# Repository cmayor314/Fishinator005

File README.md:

# Fishinator005
Fishinator005 is an **Aquaponic** system.  It is for growing both plants and fish together in a enclosed space
for the purposes of food.

## Aquaponics

Aquaponics is conservative of water; the only significant water loss is due to evaporation.
Two crops are fed for the price of one: you feed the fish and ammonia from their gills is plant food.

## What's here

The current working system is here, but still being filled in.
The documentation will take a long time.

The software/hardware includes a:

  - remote sense cluster
  
  - basic *local-to-Fishinator* control system running directly on Raspberry Pi + some hardware
  
  - basic RESTful interface on Raspberry Pi for control by Supervisor Flows
  
  - Supervisor system Control and Analysis on a remote machine with more computing power available
  
  - web-based UI

## Components:

### Supervisor 
- Control and analysis from remote machine with better computational ability via node-red and node.js

### FishinatorPi 
- currently Raspberry-pi implmentation of Fishinator direct control via node-red and node.js

### RemoteSense 
- Atmel Mega328p implementation of reading local sensors, sent directly to Fishinator
			-KiCAD schematic files (schematic complete, placement and routing not started)
			-arduino-interface code

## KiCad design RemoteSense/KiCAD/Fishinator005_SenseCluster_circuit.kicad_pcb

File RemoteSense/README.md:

This directory contains the **Remote Sense Cluster** for the fishinator.

This Sense Cluster is "remote" in the sense that it may be placed anywhere (within bluetooth range) with respect to the FishinatorPi (which controls the Fishinator), it is not connected by wire.  The Sense Cluster *must* be reasonably attached to the Fishinator, the system for which it senses.

The Fishinator uses this remote sense cluster to get data about light levels, temperatures, and a water-depth measurement.  Also available are voltage levels from the remote sense cluster circuit.

Via bluetooth serial, the remote sense cluster sends its data to the FishinatorPi device.

This directory includes:

  - the arduino-interface code (C/C++) for the ATMEL 328p microcontroller.
  - A subdirectory holds the (current state of) the KiCAD files for manufacturing a remote sense cluster printed circuit board.  

The KiCAD design is based on the prototype-board impementation with the Fishinator.

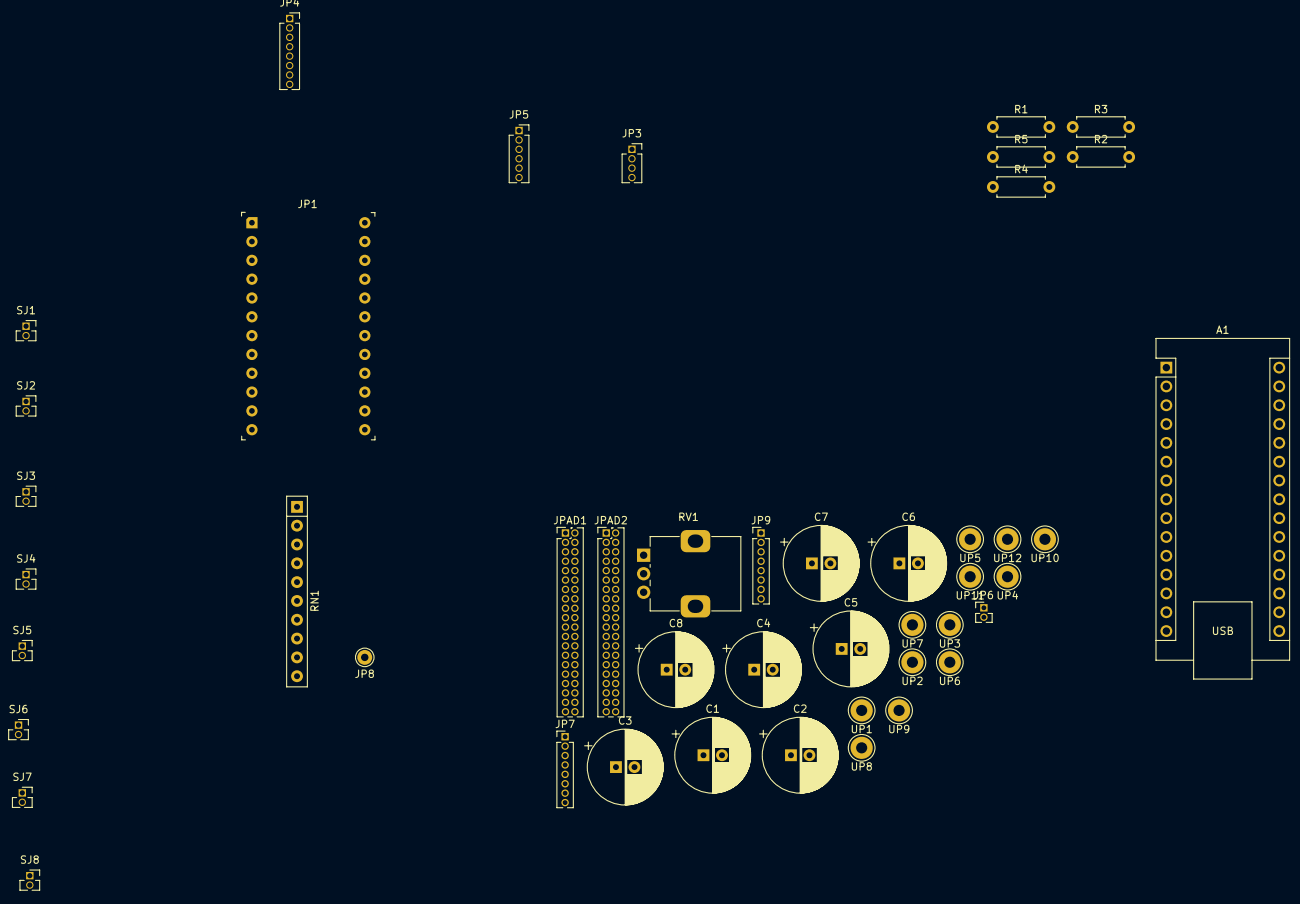
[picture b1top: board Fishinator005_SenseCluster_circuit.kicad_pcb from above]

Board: 2 copper layers, 46 parts (0 on the bottom side), 42 nets, no tracks yet.

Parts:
A1: Arduino_Nano_v3.x; Arduino_Nano
C1, C2, C3, C4, C5, C6, C7, C8: C_Polarized_US; CP_Radial_D10.0mm_P2.50mm
JP1: A_24-LC-TT; Socket_DIP-24_15.24mm_Conn
JP3: Conn_01x04_Male; PinSocket_1x04_P1.27mm_Vertical
JP4: Conn_01x08_Female; PinSocket_1x08_P1.27mm_Vertical
JP5: Conn_01x06_Female; PinSocket_1x06_P1.27mm_Vertical
JP6: Conn_01x02_Male; PinHeader_1x02_P1.27mm_Vertical
JP7, JP9: Conn_01x08; PinHeader_1x08_P1.27mm_Vertical
JP8: Conn_01x08; Pin_D1.0mm_L10.0mm
JPAD1, JPAD2: Conn_02x20_Counter_Clockwise; PinHeader_2x20_P1.27mm_Vertical
R1: 200R; R_Axial_DIN0207_L6.3mm_D2.5mm_P7.62mm_Horizontal
R2: 2k; R_Axial_DIN0207_L6.3mm_D2.5mm_P7.62mm_Horizontal
R3: 1k; R_Axial_DIN0207_L6.3mm_D2.5mm_P7.62mm_Horizontal
R4, R5: 0R; R_Axial_DIN0207_L6.3mm_D2.5mm_P7.62mm_Horizontal
RN1: R_Network09_US; R_Array_SIP10
RV1: 500R; Potentiometer_Alps_RK09K_Single_Vertical
SJ1, SJ2, SJ3, SJ4, SJ5, SJ6, SJ7, SJ8: Screw_Terminal_01x02; PinSocket_1x02_P1.27mm_Vertical
UP1, UP2, UP3, UP4, UP5, UP6, UP7, UP8, UP9, UP10, UP11, UP12: Conn_01x01; Pin_D1.3mm_L11.0mm_LooseFit

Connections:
+3V3: A1.17 (3V3), C1.1, C2.1, C3.1, JP1.21, JP4.7, JP7.6, RN1.1 (common)
+5V: A1.27 (+5V), C4.1, C5.1, C6.1, JP1.22, JP3.1, JP5.2
/CS: JP1.2, JP4.3, JP7.2
/DC: JP1.20, JP4.4, JP7.3, UP4.1
/EN: A1.9 (D6), JP1.19, R4.1, UP3.1
/MISO: JP1.4, JP7.8, UP5.1
/RST: JP1.1, JP4.2, JP7.1
/SCK: JP1.5, JP4.5, JP7.4
/SDA: JP1.3, JP4.6, JP7.5
/Sense1: A1.19 (A0), JP1.7, RN1.2 (R1), SJ1.2
/Sense2: A1.20 (A1), JP1.8, RN1.3 (R2), SJ2.2
/Sense3: A1.21 (A2), JP1.9, RN1.4 (R3), SJ3.2
/Sense4: A1.22 (A3), JP1.10, RN1.5 (R4), SJ4.2
/Sense5: A1.23 (A4), JP1.11, RN1.6 (R5), SJ5.2
/Sense6: A1.24 (A5), JP1.12, RN1.7 (R6), SJ6.2
/Sense7: A1.25 (A6), RN1.8 (R7), SJ7.2, UP9.1
/Sense8: A1.26 (A7), JP8.1, RN1.9 (R8), SJ8.2, UP10.1
/Vref: A1.18 (AREF), JP1.6, UP6.1
/arRx: A1.2 (D0/RX), JP1.14, JP5.4
/arTx: A1.1 (D1/TX), JP1.15, JP5.5
/echo: A1.7 (D4), JP1.17, JP6.2, R2.1, R3.1
/state: A1.6 (D3), JP1.16, R5.1, UP2.1
/trig: A1.8 (D5), JP1.18, JP3.2
GND: A1.4 (GND), A1.29 (GND), C1.2, C2.2, C3.2, C4.2, C5.2, C6.2, C7.2, C8.2, JP1.23, JP3.4, JP4.8, JP5.3, JP7.7, R1.1, R2.2, SJ1.1, SJ2.1, SJ3.1, SJ4.1, SJ5.1, SJ6.1, SJ7.1, SJ8.1
unnamed: A1.5 (D2), JP9.8
unnamed: A1.10 (D7), JP9.7
unnamed: A1.11 (D8), JP9.6
unnamed: A1.12 (D9), JP9.5
unnamed: A1.13 (D10), JP9.4
unnamed: A1.14 (D11), JP9.3
unnamed: A1.15 (D12), JP9.2
unnamed: A1.16 (D13), JP9.1
unnamed: A1.30 (VIN), UP12.1
unnamed: C7.1, UP7.1
unnamed: C8.1, UP8.1
unnamed: JP1.24, UP11.1
unnamed: JP3.3, JP6.1, R3.2
unnamed: JP4.1, RV1.2
unnamed: JP5.1, R4.2
unnamed: JP5.6, R5.2
unnamed: R1.2, RV1.1
unnamed: RN1.10 (R9), UP1.1

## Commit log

2024-12-28 first up
2024-12-28 slightly more info
2024-12-28 First add sense cluster code
2024-12-28 first add of Raspberry Pi flow code
2024-12-28 Picture of Remote Sense Cluster working prototype
2024-12-28 Update README.md
    added README info
2024-12-29 UI screencaps for Supervisor
2024-12-29 photo of prototype
2024-12-29 action pose of ui
2024-12-29 RPi Fishinator UI Dashboard
2025-01-02 upload schematic files
2025-01-02 remove accidentally included files
2025-01-02 more details about Remote Sense files
2025-01-02 Update README.md
    Added photos and more descriptions. Separated header styles
2025-01-03 adding other needed node-red config files
2025-01-05 new README file
2025-01-05 added named hardware
2025-01-05 Update README.md
    Added UI interface view
2025-01-05 Update README.md
    Added some Supervisor UI views
2025-01-05 Update README.md
    added image of schematic and photo of prototype version
2025-01-05 Update README.md
    increased exposition re: Sense Cluster
